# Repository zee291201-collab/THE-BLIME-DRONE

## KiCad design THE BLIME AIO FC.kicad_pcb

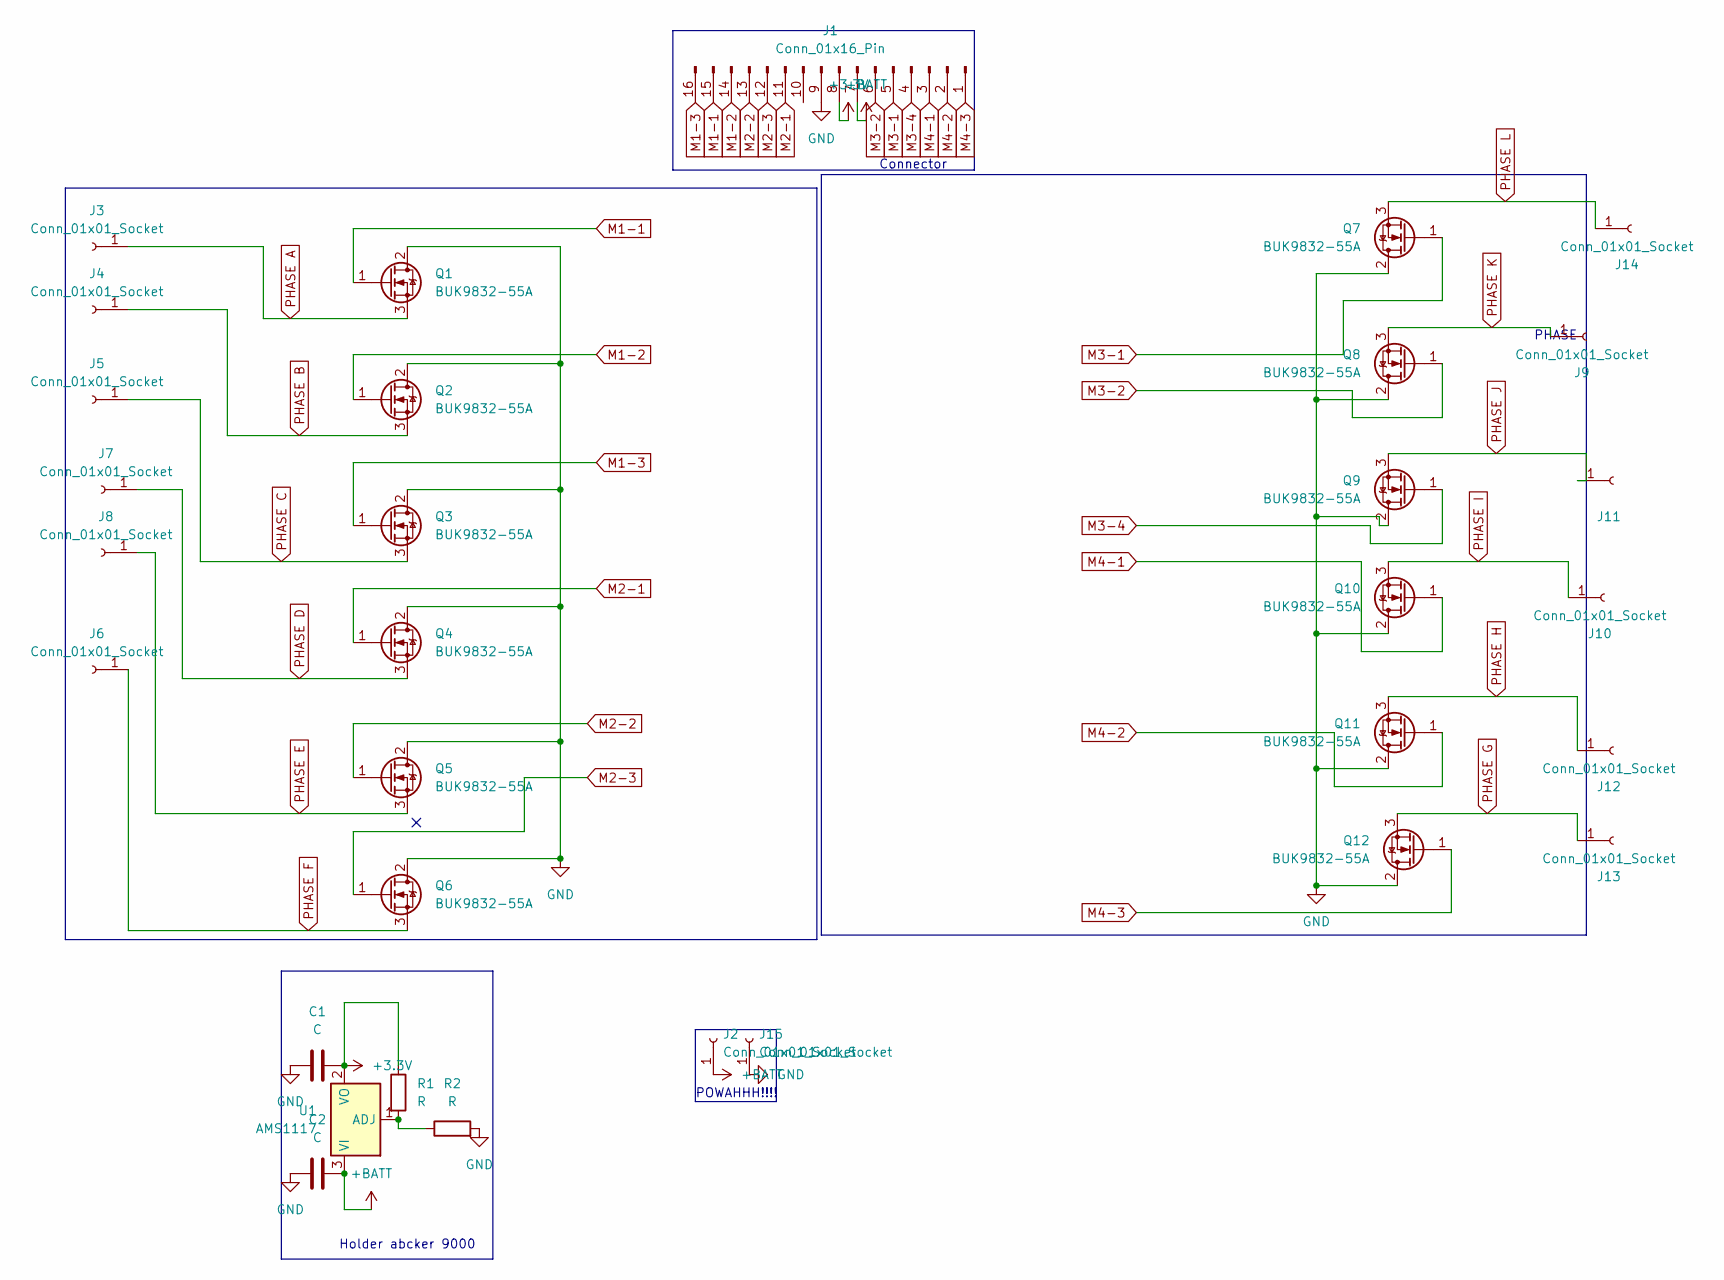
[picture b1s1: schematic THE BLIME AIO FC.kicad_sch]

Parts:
C1, C2: C; C_0805_2012Metric
J1: Conn_01x16_Pin; 100nF Cap is returning!!!!!
J2, J15: Conn_01x01_Socket; POWERPAD
J3, J4, J5, J6, J7, J8, J9, J10, J11, J12, J13, J14: Conn_01x01_Socket; TestPoint_Pad_2.0x2.0mm
Q1, Q2, Q3, Q4, Q5, Q6, Q7, Q8, Q9, Q10, Q11, Q12: BUK9832-55A; SOT-223-3_TabPin2
R1, R2: R; R_0402_1005Metric
U1: AMS1117; SOT-223-3_TabPin2

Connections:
+3.3V: C1.2, J1.8, R1.1, U1.2 (VO)
+BATT: C2.2, J1.7, J2.1, U1.3 (VI)
GND: C1.1, C2.1, J1.9, J15.1, Q1.2 (D), Q2.2 (D), Q3.2 (D), Q4.2 (D), Q5.2 (D), Q6.2 (D), Q7.2 (D), Q8.2 (D), Q9.2 (D), Q10.2 (D), Q11.2 (D), Q12.2 (D), R2.2
M1-1: J1.15, Q1.1 (G)
M1-2: J1.14, Q2.1 (G)
M1-3: J1.16, Q3.1 (G)
M2-1: J1.11, Q4.1 (G)
M2-2: J1.13, Q5.1 (G)
M2-3: J1.12, Q6.1 (G)
M3-1: J1.5, Q7.1 (G)
M3-2: J1.6, Q8.1 (G)
M3-4: J1.4, Q9.1 (G)
M4-1: J1.3, Q10.1 (G)
M4-2: J1.2, Q11.1 (G)
M4-3: J1.1, Q12.1 (G)
unnamed: R1.2, R2.1, U1.1 (ADJ)
PHASE A: J3.1, Q1.3 (S)
PHASE B: J4.1, Q2.3 (S)
PHASE C: J5.1, Q3.3 (S)
PHASE D: J7.1, Q4.3 (S)
PHASE E: J8.1, Q5.3 (S)
PHASE F: J6.1, Q6.3 (S)
PHASE G: J13.1, Q12.3 (S)
PHASE H: J12.1, Q11.3 (S)
PHASE I: J10.1, Q10.3 (S)
PHASE J: J11.1, Q9.3 (S)
PHASE K: J9.1, Q8.3 (S)
PHASE L: J14.1, Q7.3 (S)

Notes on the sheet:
Connector
POWAHHH!!!!
Holder abcker 9000
PHASE

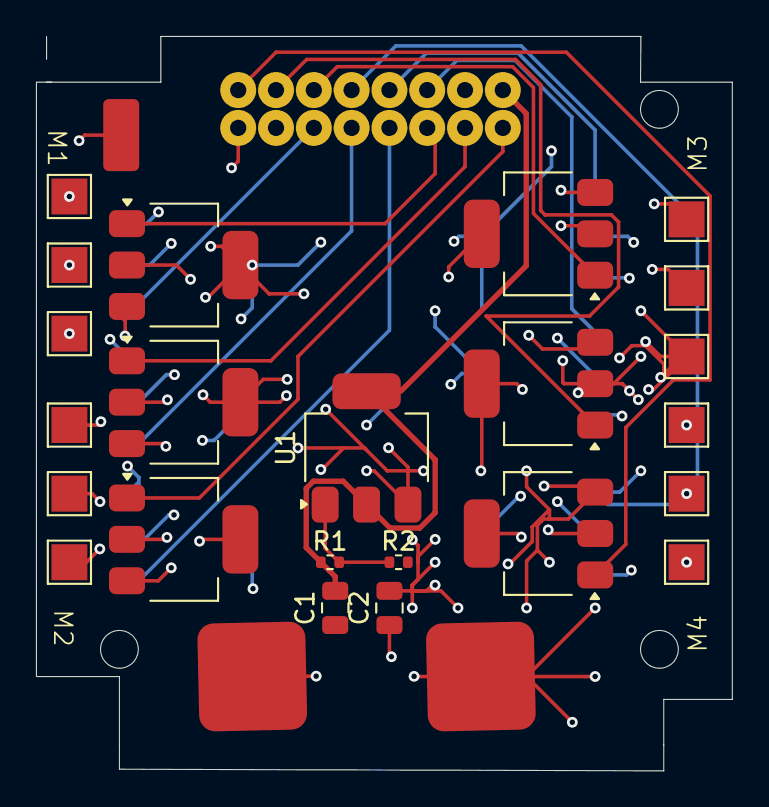
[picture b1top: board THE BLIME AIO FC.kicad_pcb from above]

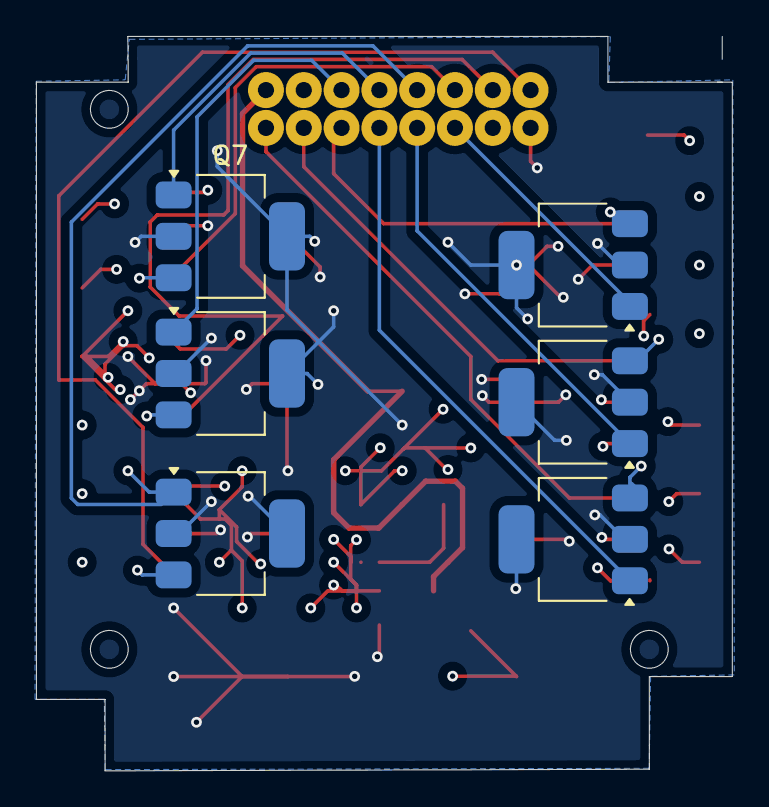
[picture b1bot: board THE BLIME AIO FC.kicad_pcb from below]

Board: 6 copper layers, 38.7 x 40.8 mm, 32 parts (6 on the bottom side), 28 nets.
